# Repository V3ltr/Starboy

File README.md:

# Starboy

This is a Starboy and no, not a starbie :] 
This project only includes only the PCB but in my other projects you can find the enclosure and etc.
It is a device that senses heat, moisture and has a face to show what its feeling.
I made it because I wanted my bag to have more of a personality with interactive emotions and more! (100% not the printer ;] halflife.hackclub.com!!!)
It does look like any other Starboy but it features a underwater theme that also has a custom interface and 3D model themed with the ocean!
Ive always wanted a starbie, but here in the Czech Republic 2-14000,-czk is criminal so im grateful hackclub is helping me in this sense.
Also for the kind reviewer working on my project... please note that the originality in sin the UI+Enclosure+Eye theme
Item,Qty,Supplier,Cost/item,Total Cost,link
Pin Header 1x4,1,RPIshop,$5.18,$5.18,https://rpishop.cz/headery/552-40-pinovy-jednoradkovy-nastavec.html
metal film resistor 1%,1,Dratek,$0.36,$0.36,https://dratek.cz/arduino-platforma/174925-metalizovany-rezistor-22k-5w-1.html
DHT11,1,Dratek,$3.82,$3.82,https://dratek.cz/arduino-platforma/829-dht11-teplomer-a-vlhkomer-digitalni.html
0.96 Inch OLED Display Module SSD1306 I2C,1,Dratek,$4.23,$4.23,https://dratek.cz/arduino-platforma/1569-iic-i2c-oled-display-0-96-128x64-bily.html
PCB,1,JLCPCB,$15.00,$15.00,https://jlcpcb.com
MPU 6050,1,Dratek,$4.46,$4.46,https://dratek.cz/arduino-platforma/830-iic-i2c-gyroskop-akcelerometr-modul-mpu-6050.html
Estimated total shipping $32.00

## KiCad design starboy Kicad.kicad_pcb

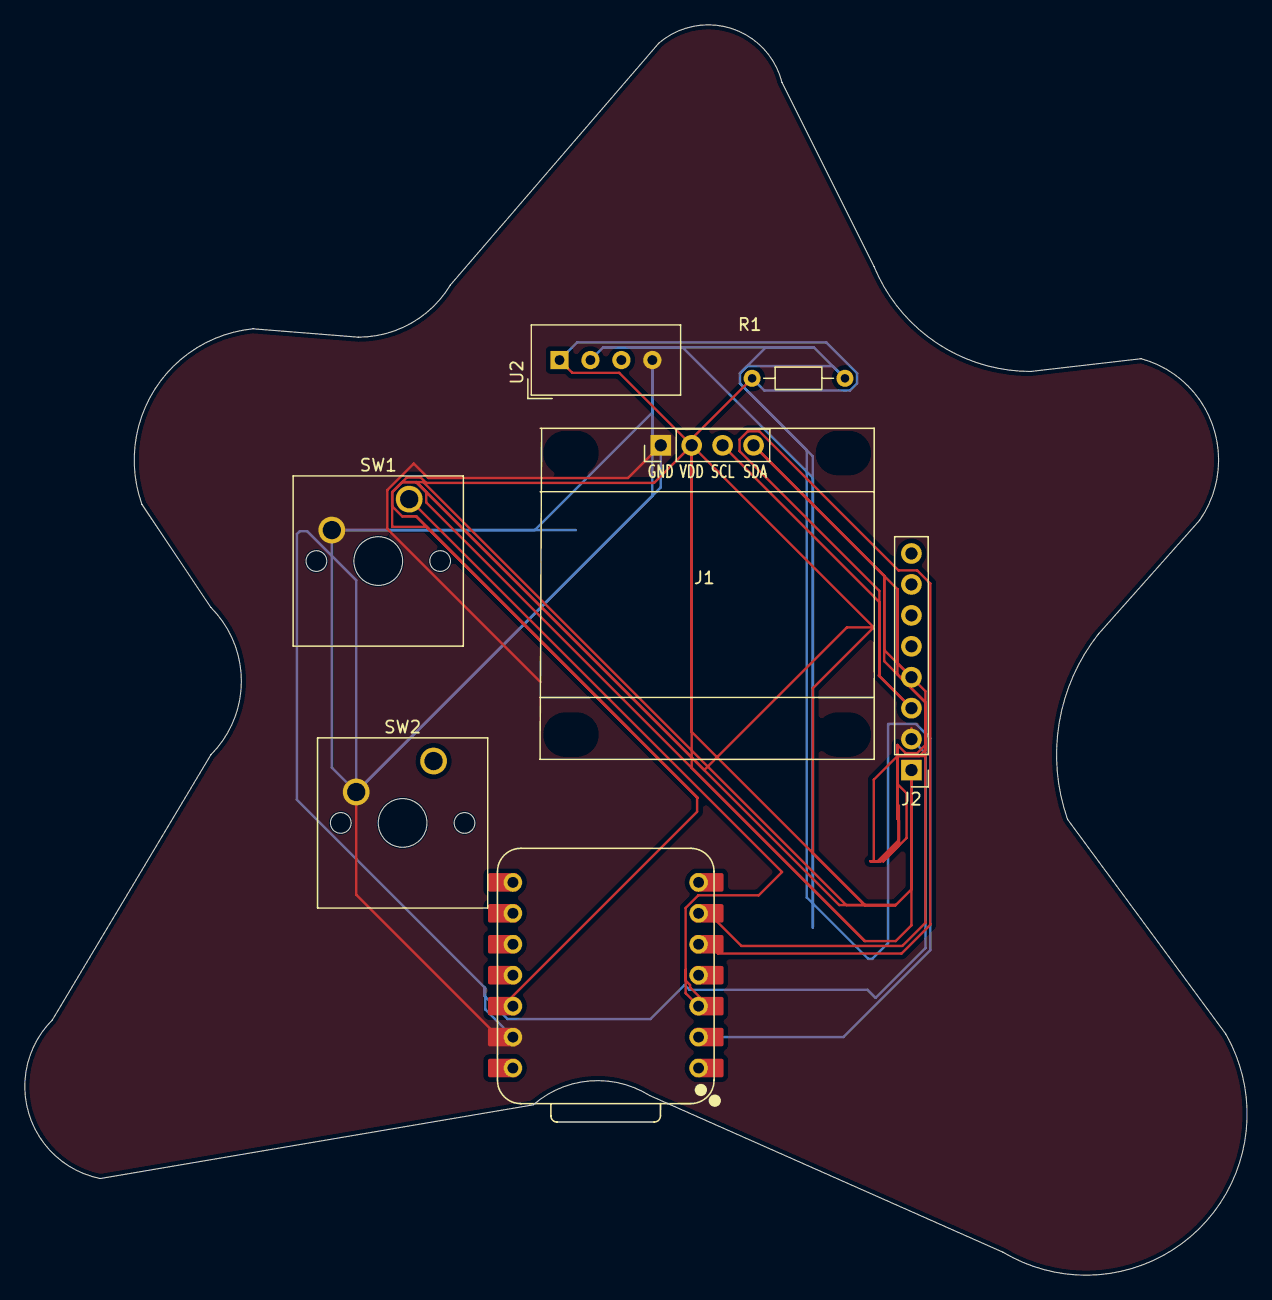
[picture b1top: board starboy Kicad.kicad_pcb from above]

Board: 2 copper layers, 100.3 x 102.6 mm, 7 parts (0 on the bottom side), 6 nets.

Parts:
J1: Conn_01x04_Pin; Display_128x64_096_I2C
J2: Conn_01x08_Pin; PinHeader_1x08_P2.54mm_Vertical
R1: 10K; R_Axial_DIN0204_L3.6mm_D1.6mm_P7.62mm_Horizontal
SW1, SW2: SW_Push; SW_Cherry_MX_1.00u_PCB
U1: XIAO-ESP32-C3-SMD; XIAO-ESP32-C6-DIP
U2: DHT11; Aosong_DHT11_5.5x12.0_P2.54mm

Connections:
+3.3V: J1.2, J2.1, R1.1, U1.12 (3V3_OUT), U2.1 (VDD)
/DHT11 DATA: R1.2, U1.2 (D1), U2.2 (DATA)
/GPIO2: SW1.1, U1.3 (D2)
/SCL: J1.3, J2.3, U1.5 (D4)
/SDA: J1.4, J2.4, U1.6 (D5)
GND: J1.1, J2.2, SW1.2, SW2.2, U1.13 (GND), U2.4 (GND)
